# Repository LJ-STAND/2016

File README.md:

# 2016
Archive of all repos from 2016

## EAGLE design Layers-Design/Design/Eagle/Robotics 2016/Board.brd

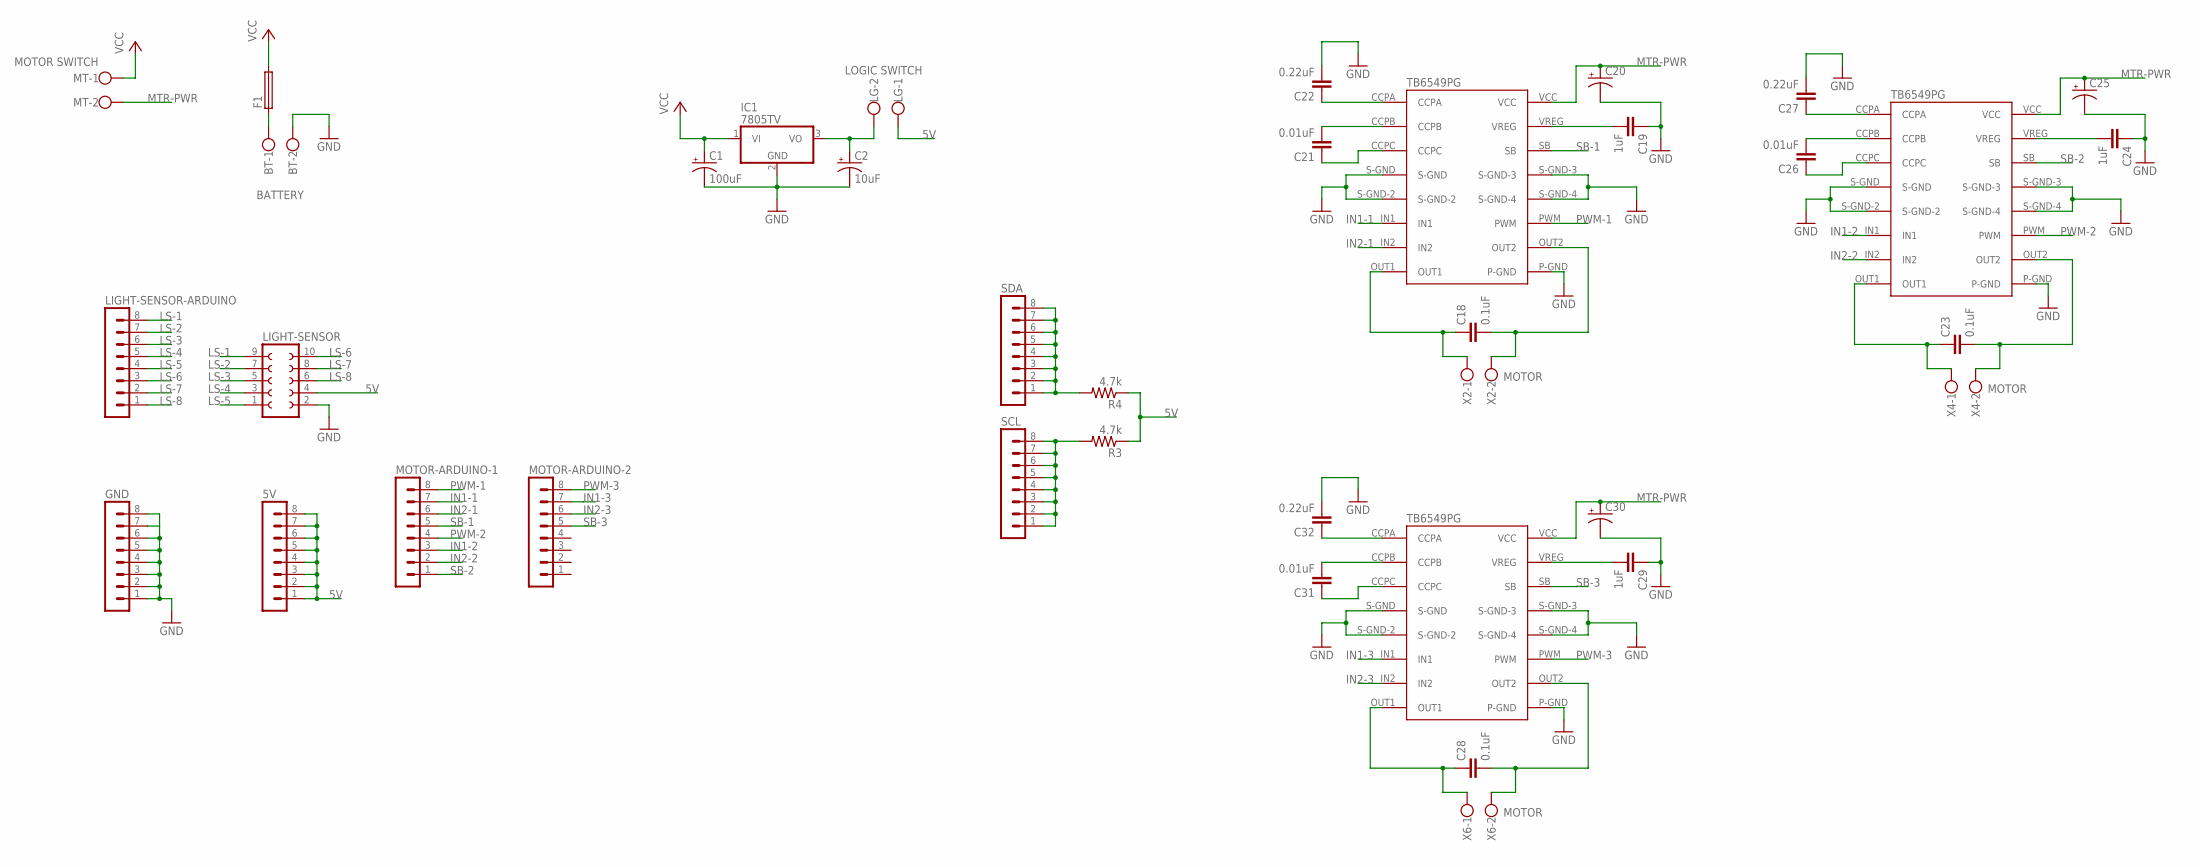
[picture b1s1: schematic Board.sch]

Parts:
5V: MA08-1
BT: W237-102
C1: 100uF; E3,5-8
C2: 10uF; E3,5-8
C18, C23, C28: 0.1uF; YC7B5
C19, C24, C29: 1uF; YC7B5
C20, C25, C30: CPOL-USE3.5-8; E3,5-8
C21, C26, C31: 0.01uF; YC7B5
C22, C27, C32: 0.22uF; YC7B5
F1: GSH15
GND: MA08-1
IC1: 7805TV; TO220V
LG: W237-102
LIGHT-SENSOR: FE05-2
LIGHT-SENSOR-ARDUINO: MA08-1
MOTOR-ARDUINO-1, MOTOR-ARDUINO-2: MA08-1
MT: W237-102
R3, R4: 4.7k; 0207/10
SCL: MA08-1
SDA: MA08-1
U$4, U$5, U$6: TB6549PG
X2, X4, X6: W237-102

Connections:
1: C2.+, IC1.3 (VO), LG.2
5V: 5V.1, 5V.2, 5V.3, 5V.4, 5V.5, 5V.6, 5V.7, 5V.8, LG.1, LIGHT-SENSOR.4, R3.1, R4.1
GND: BT.2, C1.-, C2.-, C19.1, C20.-, C22.2, C24.1, C25.-, C27.2, C29.1, C30.-, C32.2, GND.1, GND.2, GND.3, GND.4, GND.5, GND.6, GND.7, GND.8, IC1.2 (GND), LIGHT-SENSOR.2, U$4.P-GND, U$4.S-GND, U$4.S-GND-2, U$4.S-GND-3, U$4.S-GND-4, U$5.P-GND, U$5.S-GND, U$5.S-GND-2, U$5.S-GND-3, U$5.S-GND-4, U$6.P-GND, U$6.S-GND, U$6.S-GND-2, U$6.S-GND-3, U$6.S-GND-4; also elsewhere on the board
IN1-1: MOTOR-ARDUINO-1.7, U$4.IN1; also elsewhere on the board
IN1-2: MOTOR-ARDUINO-1.3, U$5.IN1; also elsewhere on the board
IN1-3: MOTOR-ARDUINO-2.7, U$6.IN1; also elsewhere on the board
IN1-4: MOTOR-ARDUINO-2.3; also elsewhere on the board
IN2-1: MOTOR-ARDUINO-1.6, U$4.IN2; also elsewhere on the board
IN2-2: MOTOR-ARDUINO-1.2, U$5.IN2; also elsewhere on the board
IN2-3: MOTOR-ARDUINO-2.6, U$6.IN2; also elsewhere on the board
IN2-4: MOTOR-ARDUINO-2.2; also elsewhere on the board
LS-1: LIGHT-SENSOR.9, LIGHT-SENSOR-ARDUINO.8; also elsewhere on the board
LS-2: LIGHT-SENSOR.7, LIGHT-SENSOR-ARDUINO.7; also elsewhere on the board
LS-3: LIGHT-SENSOR.5, LIGHT-SENSOR-ARDUINO.6; also elsewhere on the board
LS-4: LIGHT-SENSOR.3, LIGHT-SENSOR-ARDUINO.5; also elsewhere on the board
LS-5: LIGHT-SENSOR.1, LIGHT-SENSOR-ARDUINO.4; also elsewhere on the board
LS-6: LIGHT-SENSOR.10, LIGHT-SENSOR-ARDUINO.3; also elsewhere on the board
LS-7: LIGHT-SENSOR.8, LIGHT-SENSOR-ARDUINO.2; also elsewhere on the board
LS-8: LIGHT-SENSOR.6, LIGHT-SENSOR-ARDUINO.1; also elsewhere on the board
unnamed 19: BT.1, F1.1; also elsewhere on the board
unnamed: R3.2, SCL.1, SCL.2, SCL.3, SCL.4, SCL.5, SCL.6, SCL.7, SCL.8
unnamed: R4.2, SDA.1, SDA.2, SDA.3, SDA.4, SDA.5, SDA.6, SDA.7, SDA.8
unnamed: C22.1, U$4.CCPA
unnamed: C21.2, U$4.CCPB
unnamed: C21.1, U$4.CCPC
unnamed: C18.2, U$4.OUT2, X2.2
unnamed: C18.1, U$4.OUT1, X2.1
unnamed: C19.2, U$4.VREG
unnamed: C27.1, U$5.CCPA
unnamed: C26.2, U$5.CCPB
unnamed: C26.1, U$5.CCPC
unnamed: C23.2, U$5.OUT2, X4.2
unnamed: C23.1, U$5.OUT1, X4.1
unnamed: C24.2, U$5.VREG
unnamed: C32.1, U$6.CCPA
unnamed: C31.2, U$6.CCPB
unnamed: C31.1, U$6.CCPC
unnamed: C28.2, U$6.OUT2, X6.2
unnamed: C28.1, U$6.OUT1, X6.1
unnamed: C29.2, U$6.VREG
PWM-1: MOTOR-ARDUINO-1.8, U$4.PWM; also elsewhere on the board
PWM-2: MOTOR-ARDUINO-1.4, U$5.PWM; also elsewhere on the board
PWM-3: MOTOR-ARDUINO-2.8, U$6.PWM; also elsewhere on the board
PWM-4: MOTOR-ARDUINO-2.4; also elsewhere on the board
SB-1: MOTOR-ARDUINO-1.5, U$4.SB; also elsewhere on the board
SB-2: MOTOR-ARDUINO-1.1, U$5.SB; also elsewhere on the board
SB-3: MOTOR-ARDUINO-2.5, U$6.SB; also elsewhere on the board
SB-4: MOTOR-ARDUINO-2.1; also elsewhere on the board
VCC: C1.+, F1.2, IC1.1 (VI), MT.1; also elsewhere on the board

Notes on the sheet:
MOTOR SWITCH
LOGIC SWITCH
BATTERY
MOTOR

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
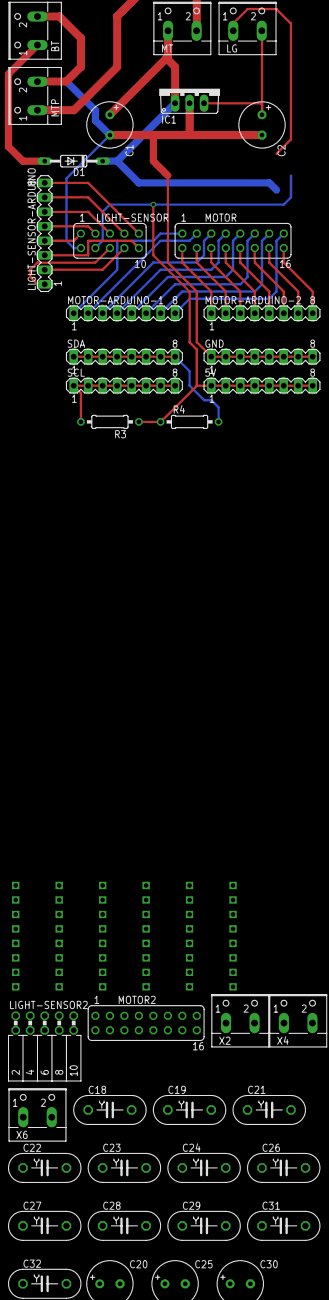
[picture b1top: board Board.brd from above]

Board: 2 copper layers, 42 parts (0 on the bottom side), 51 nets.

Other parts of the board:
D1: 1N4148DO35-10; DO35-10
LIGHT-SENSOR2: FE05-2W
MOTOR, MOTOR2: FE08-2
MTP: W237-102

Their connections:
GND: LIGHT-SENSOR2.2, MTP.2; also elsewhere on the board
IN1-1: MOTOR.13, MOTOR2.4; also elsewhere on the board
IN1-2: MOTOR.5, MOTOR2.12; also elsewhere on the board
IN1-3: MOTOR.14, MOTOR2.3; also elsewhere on the board
IN1-4: MOTOR.6, MOTOR2.11; also elsewhere on the board
IN2-1: MOTOR.11, MOTOR2.6; also elsewhere on the board
IN2-2: MOTOR.3, MOTOR2.14; also elsewhere on the board
IN2-3: MOTOR.12, MOTOR2.5; also elsewhere on the board
IN2-4: MOTOR.4, MOTOR2.13; also elsewhere on the board
LS-1: LIGHT-SENSOR2.9; also elsewhere on the board
LS-2: LIGHT-SENSOR2.7; also elsewhere on the board
LS-3: LIGHT-SENSOR2.5; also elsewhere on the board
LS-4: LIGHT-SENSOR2.3; also elsewhere on the board
LS-5: LIGHT-SENSOR2.1; also elsewhere on the board
LS-6: LIGHT-SENSOR2.10; also elsewhere on the board
LS-7: LIGHT-SENSOR2.8; also elsewhere on the board
LS-8: LIGHT-SENSOR2.6; also elsewhere on the board
unnamed 19: D1.A; also elsewhere on the board
PWM-1: MOTOR.15, MOTOR2.2; also elsewhere on the board
PWM-2: MOTOR.7, MOTOR2.10; also elsewhere on the board
PWM-3: MOTOR.16, MOTOR2.1; also elsewhere on the board
PWM-4: MOTOR.8, MOTOR2.9; also elsewhere on the board
SB-1: MOTOR.9, MOTOR2.8; also elsewhere on the board
SB-2: MOTOR.1, MOTOR2.16; also elsewhere on the board
SB-3: MOTOR.10, MOTOR2.7; also elsewhere on the board
SB-4: MOTOR.2, MOTOR2.15; also elsewhere on the board
VCC: D1.C, LIGHT-SENSOR2.4; also elsewhere on the board

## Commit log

2016-10-19 this is an archived version
